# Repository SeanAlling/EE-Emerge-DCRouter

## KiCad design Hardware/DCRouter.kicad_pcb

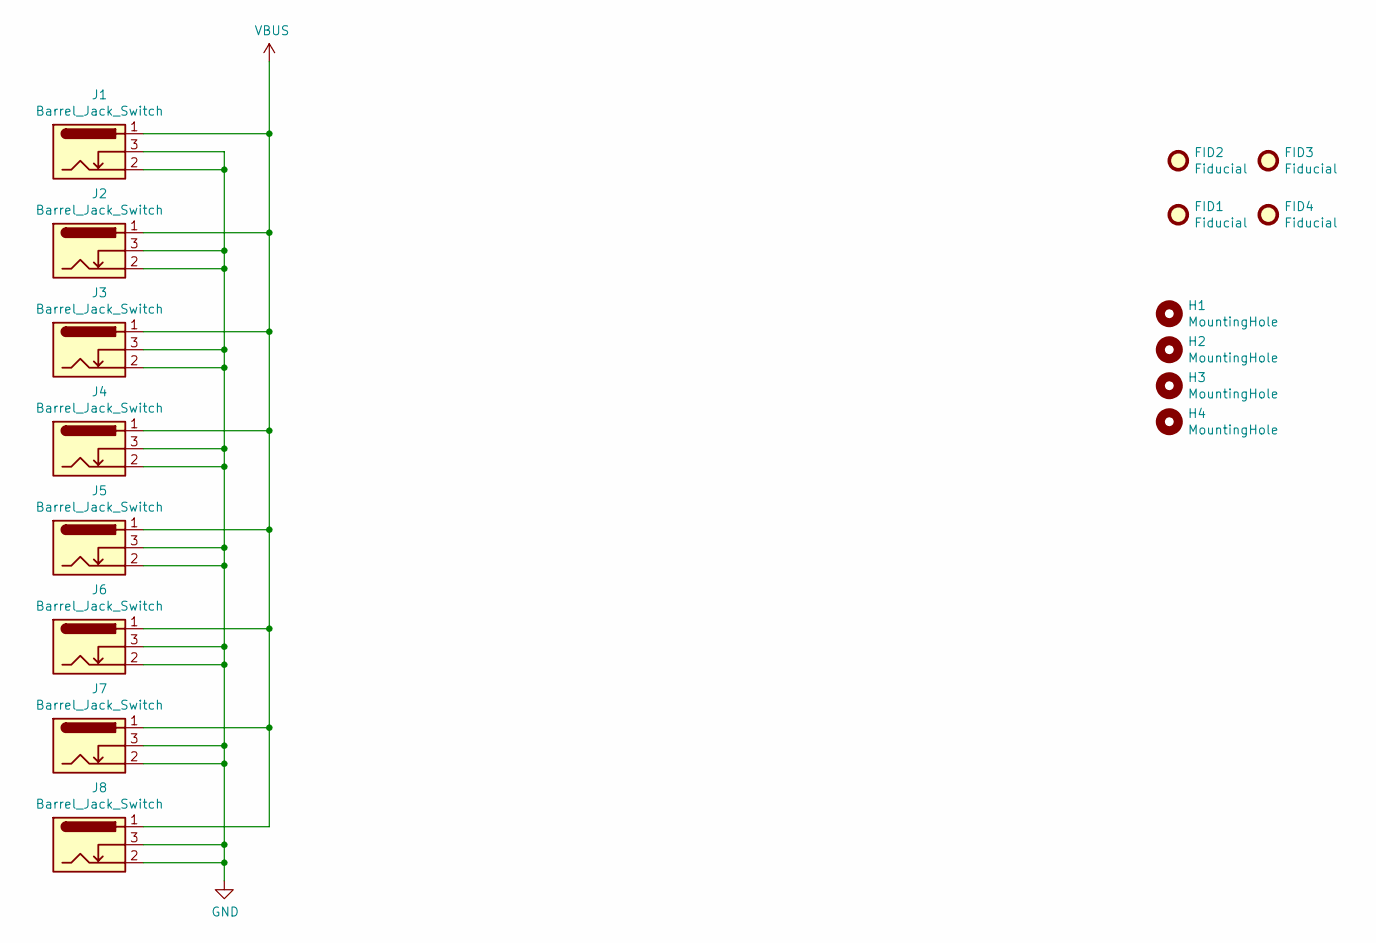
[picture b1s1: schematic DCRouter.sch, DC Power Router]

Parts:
FID1, FID2, FID3, FID4: Fiducial; Fiducial_0.5mm_Mask1.5mm
H1, H2, H3, H4: MountingHole; MountingHole_3.5mm
J1, J2, J3, J4, J5, J6, J7, J8: Barrel_Jack_Switch; BarrelJack_CUI_PJ-102AH_Horizontal

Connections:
GND: J1.2, J1.3, J2.2, J2.3, J3.2, J3.3, J4.2, J4.3, J5.2, J5.3, J6.2, J6.3, J7.2, J7.3, J8.2, J8.3
VBUS: J1.1, J2.1, J3.1, J4.1, J5.1, J6.1, J7.1, J8.1

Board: 2 copper layers, 16 parts (2 on the bottom side), 2 nets, no tracks yet.
